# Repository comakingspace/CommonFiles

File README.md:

# CommonFiles
This repository can serve as a place for files relevant for the CoMakingSpace

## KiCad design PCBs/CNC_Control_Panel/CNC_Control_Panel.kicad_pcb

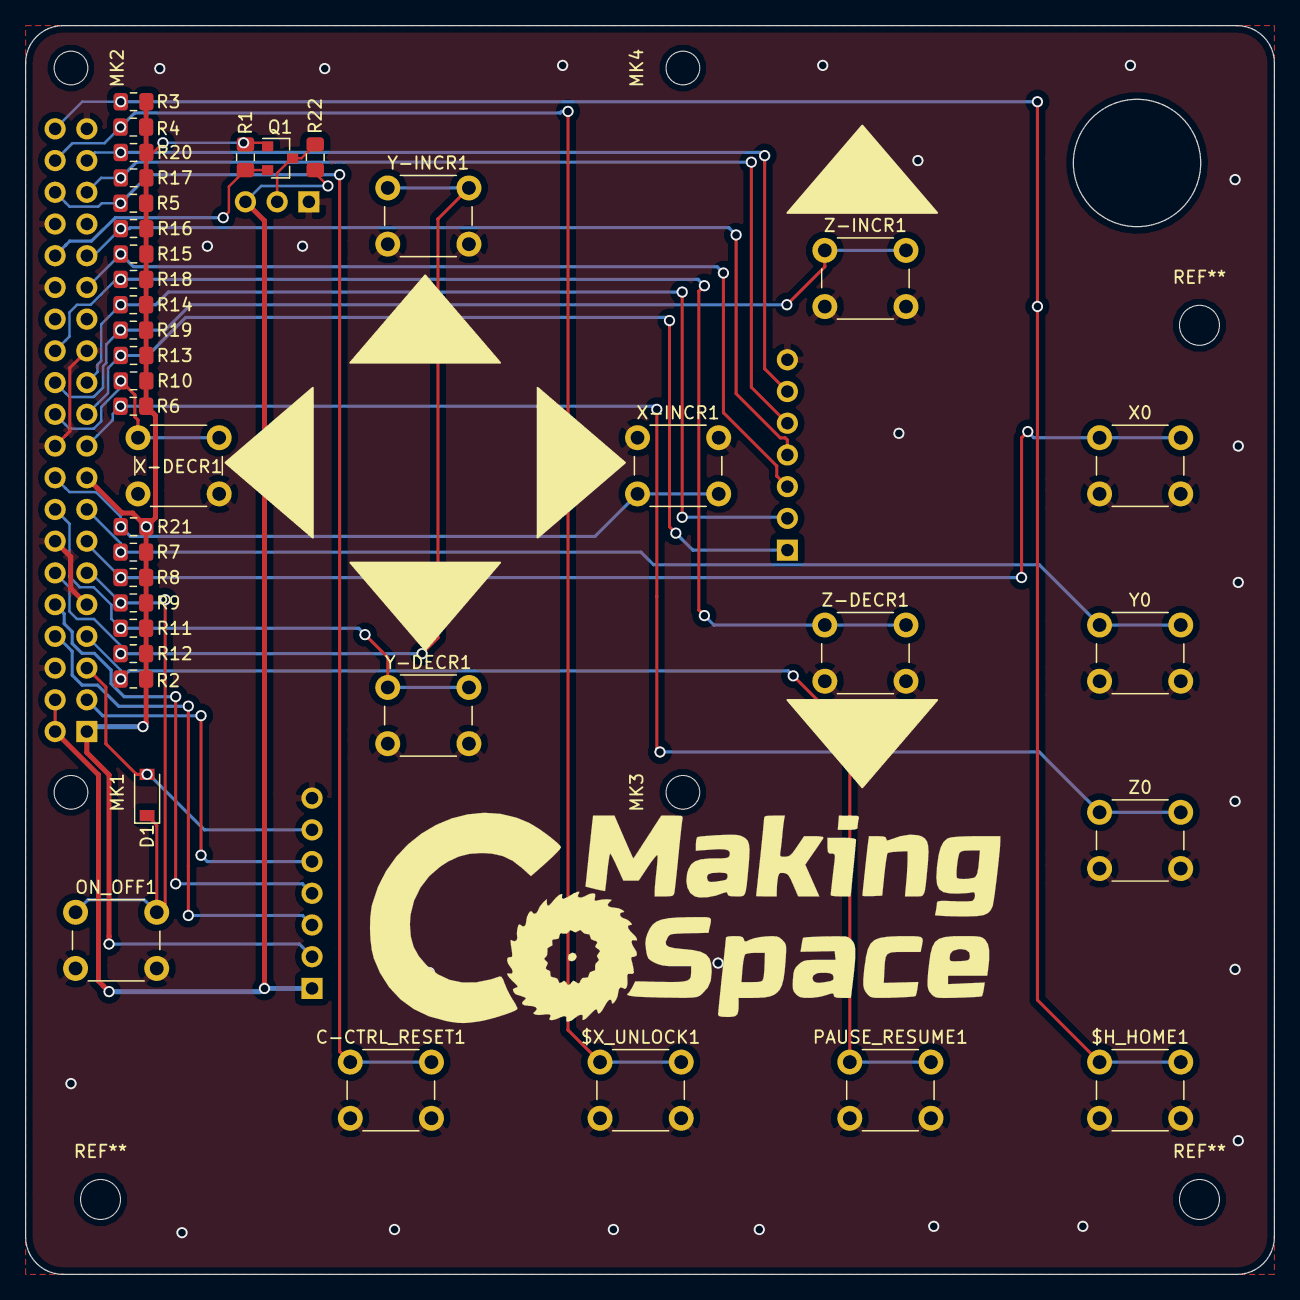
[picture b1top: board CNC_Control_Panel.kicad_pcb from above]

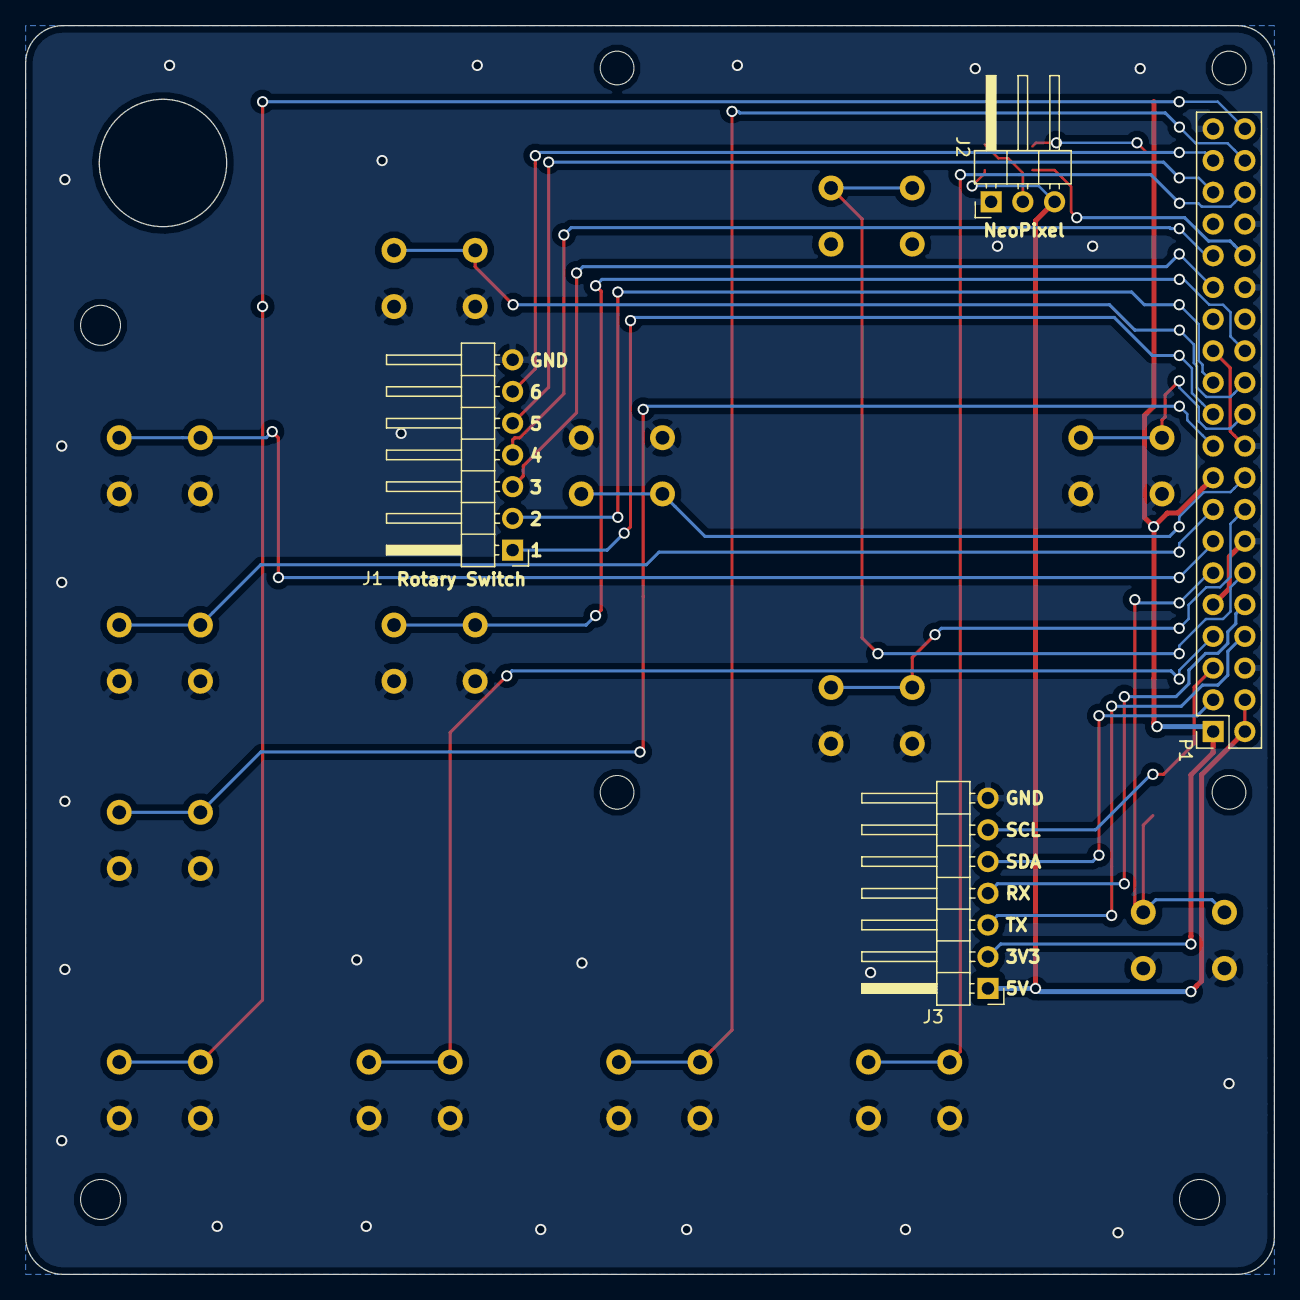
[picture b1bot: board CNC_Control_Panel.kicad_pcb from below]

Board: 2 copper layers, 100.0 x 100.0 mm, 46 parts (4 on the bottom side), 29 nets.

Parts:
$H_HOME1: SW_Push; SW_PUSH_6mm
$X_UNLOCK1: SW_Push; SW_PUSH_6mm
C-CTRL_RESET1: SW_Push; SW_PUSH_6mm
D1: 1N4148W; D_SOD-123
J1, J3: Conn_01x07_Male; PinHeader_1x07_P2.54mm_Horizontal
J2: Conn_01x03_Male; PinHeader_1x03_P2.54mm_Horizontal
MK1, MK2, MK3, MK4: M2.5; MountingHole_2.7mm_M2.5
ON_OFF1: SW_Push; SW_PUSH_6mm
P1: Conn_02x20_Odd_Even; PinSocket_2x20_P2.54mm_Vertical
PAUSE_RESUME1: SW_Push; SW_PUSH_6mm
Q1: BSS138; SOT-23
R1, R2, R3, R4, R5, R6, R7, R8, R9, R10, R11, R12, R13, R14, R15, R16, R17, R18, R19, R20, R21, R22: 10k; R_0805_2012Metric_Pad1.15x1.40mm_HandSolder
X0: SW_Push; SW_PUSH_6mm
X-DECR1: SW_Push; SW_PUSH_6mm
X-INCR1: SW_Push; SW_PUSH_6mm
Y0: SW_Push; SW_PUSH_6mm
Y-DECR1: SW_Push; SW_PUSH_6mm
Y-INCR1: SW_Push; SW_PUSH_6mm
Z0: SW_Push; SW_PUSH_6mm
Z-DECR1: SW_Push; SW_PUSH_6mm
Z-INCR1: SW_Push; SW_PUSH_6mm

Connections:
+3V3: J3.2, P1.1, P1.17, Q1.1, R1.1, R2.1, R3.1, R4.1, R5.1, R6.1, R7.1, R8.1, R9.1, R10.1, R11.1, R12.1, R13.1, R14.1, R15.1, R16.1, R17.1, R18.1, R19.1, R20.1, R21.1
+5V: J2.3, J3.1, P1.2, P1.4, R22.1
/GPIO2(SDA1): J3.5, P1.3
/GPIO3(SCL1): D1.2, J3.6, P1.5
/GPIO4(GCLK): P1.7, PAUSE_RESUME1.1, R2.2
/GPIO5: J1.3, P1.29, R15.2
/GPIO6: J1.4, P1.31, R16.2
/GPIO7(SPI1_CE_N): P1.26, R18.2, Z-DECR1.1
/GPIO8(SPI0_CE_N): P1.24, R19.2, Z-INCR1.1
/GPIO9(SPI0_MISO): J1.1, P1.21, R13.2
/GPIO10(SPI0_MOSI): P1.19, R6.2, Z0.1
/GPIO11(SPI0_SCK): J1.2, P1.23, R14.2
/GPIO12(PWM0): P1.32, Q1.2, R1.2
/GPIO14(TXD0): J3.3, P1.8
/GPIO15(RXD0): J3.4, P1.10
/GPIO16: C-CTRL_RESET1.1, P1.36, R5.2
/GPIO17(GEN0): D1.1, ON_OFF1.1, P1.11, R9.2
/GPIO18(GEN1)(PWM0): P1.12, R12.2, Y-INCR1.1
/GPIO19(SPI1_MISO): J1.5, P1.35, R17.2
/GPIO20(SPI1_MOSI): $X_UNLOCK1.1, P1.38, R4.2
/GPIO21(SPI1_SCK): $H_HOME1.1, P1.40, R3.2
/GPIO22(GEN3): P1.15, R7.2, Y0.1
/GPIO23(GEN4): P1.16, R11.2, Y-DECR1.1
/GPIO24(GEN5): P1.18, R21.2, X-INCR1.2
/GPIO25(GEN6): P1.22, R10.2, X-DECR1.1
/GPIO26: J1.6, P1.37, R20.2
/GPIO27(GEN2): P1.13, R8.2, X0.1
GND: $H_HOME1.2, $X_UNLOCK1.2, C-CTRL_RESET1.2, J1.7, J2.1, J3.7, ON_OFF1.2, P1.6, P1.9, P1.14, P1.20, P1.25, P1.30, P1.34, P1.39, PAUSE_RESUME1.2, X0.2, X-DECR1.2, X-INCR1.1, Y0.2, Y-DECR1.2, Y-INCR1.2, Z0.2, Z-DECR1.2, Z-INCR1.2
unnamed: J2.2, Q1.3, R22.2

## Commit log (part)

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2018-06-28 Added files for pegboard holder in the CNC Room
2018-07-04 added STEP file for the 9mm CNC clamps
2018-07-04 added STEP file for the 9mm thick CNC clamps
2018-07-05 publishing wikicrawler
2018-07-11 Adding help the space
2018-07-11 added Logos in PNG and SVG
2018-07-12 deleting old stuff
2018-07-12 new version
2018-07-18 Added filesÂ§
2018-07-20 Added QR Code description Added arguments to the wikicrawler script
2018-07-24 Added files for the door handles
2018-07-24 Included arguments and a little help text
2018-07-27 Added the mediawiki stylesheet and fixed the bug with spaces
2018-07-27 Removed (?) & not outputting prettified html anymore due to a bug
2018-08-02 Removing html files
2018-08-02 adding the qr-code html files to gitignore
2018-08-02 Added requirements.txt and extended argument help
2018-08-20 Added Vacuum Cleaner Adapter
2018-08-22 can't spell
2018-08-22 added Dust shoe files
2018-09-11 Added Dust Adapter files
2018-09-19 Bandsaw files uploaded
    Aris forced me to do it...
2018-09-30 Adding the control panel
2018-09-30 started cleaning up the schematic and added new functions
2018-10-01 Cleanup
2018-10-01 Basic Schematic
2018-10-01 stupid .DS_Store files
2018-10-01 added pdf plot of schematic
2018-10-01 .pro file updated
2018-10-01 finished schematic and initial layout
2018-10-01 forgot to remove a merge conflict
2018-10-02 added external pullup resistors
2018-10-02 new layout with a 100x100mm board design and cutout for a 8mm rotatary switch
2018-10-02 fixed "item on disabled layer" DRC error
2018-10-02 added plots
2018-10-03 reduced sheet size to A4
2018-10-07 replaced the normal LED with a header for NeoPixels
2018-10-07 added GPIO3 to the OnOff button via a diode to allow for the Pi to be turned on
2018-10-07 added header for serial and I2C
2018-10-07 updated layout to the new changes
2018-10-07 updated schematic
2018-10-07 added better silkscreen labeling & logo
2018-10-07 updated 3D renders
2018-10-09 generated Gerber files
2018-10-12 resolving merge conflicts in wikicrawler
2018-10-15 added digital WorkBee wiring diagram
2018-10-15 added gerbers as ZIP
2018-10-15 Updated Verdrahtungsplan
2018-10-15 Added beam support files
2018-10-29 Update of requests due to security alert
2019-02-03 Update README.MD
    linked Category:MissingQR in the wiki
2019-02-17 Create 32" E-ink templates
2019-03-10 added the charset for firefox and IE compatibility
2019-03-31 Added Project Crawling. Needs some refactoring
2019-04-07 Project Pictures for the wall work
2019-05-01 cleanup of requirements
2019-05-15 updated Area Patron Template
    added QR-code to the issue tracker, placeholders for the second person and generally tried to reword in a lighter tone
2019-08-10 poster for the 2018 open day
    "1 Jahr offene Werkstatt in Heidelberg"
2020-03-03 added Tor4 poster
2020-04-16 Added New Map
2020-04-23 Rename Printouts/Businesscard_Map.svg to Printouts/Businesscards&Flyers/Businesscard_Arrows.svg
2020-05-20 Create README.md
    basically a link to the wiki
2020-05-20 current version to the best of my knowledge
    (saved "compressed")
2020-09-30 Scheppach Tiefenstop Ersatzteil
2021-07-11 NetworkDiagram.drawio
2021-07-11 Added NetworkDiagram.drawio
2021-07-19 added pdf version
2021-10-05 switch project crawling to SMW-based solution
2022-02-27 fixed PLZ to 69123
2022-02-27 updated PLZ
2022-03-20 converted to curves for font independence
2022-05-29 Wiki_Location_Plan.drawio
2022-05-29 Creation
2022-05-29 Rename Untitled Diagram.drawio to Wiki_Locations.drawio
2022-07-13 Update Wiki_Locations.drawio -> Grinding Table
2022-08-30 Add files via upload
    "photo" render of the May 2020 version
2022-10-03 Fusion360 machine file for Kress CNC Mill
2024-02-18 Wiki_Locations.drawio aktualisiert
2024-03-18 Add files via upload
    Martins wikicrawler bloß besser
2025-05-30 chore: add files for stuff in the kitchen
2025-06-20 New tool holder for "Jokari" wire stripper.
2025-06-20 add preview image for wire stripper tool holder
2025-06-20 Update readme.md
    add documentation for the wire stripper STL
2025-07-20 Woodster 2 BS 412: add 3D file for Festool vacuum adapter
2026-04-01 Remodelling - Big Arts Room.drawio eingefügt
2026-04-01 Remodelling - Big Arts Room.drawio aktualisiert
2026-04-13 Remodelling - Option 2.drawio eingefügt
2026-04-13 Rename Remodelling - Big Arts Room.drawio to Remodelling - Option 1.drawio
2026-06-12 Layout Suggestion for Plenum/Discussion
